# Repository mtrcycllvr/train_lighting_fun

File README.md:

## Train Car Lighting

Train Car Lighting via WS2812 based "neo pixel" like strips..
Use a couple of variable resistors to control color and brightness.
Optionally plug in LED to EOT device..

https://oshpark.com/shared_projects/cVBEIdNU 
...if you want a matching circuit board supporting Teensy 3.2 and 3.4.

Basic code is relatively simple thanks to extensive WS2812B RGB LED library support..
Read the analog values, map them to LED value ranges, push data.  Blink the
EOT device in a realistic manner..

Verision 1.3-ish..

INFO:
I purchased a USA trains "Extended Vision Caboose",
http://www.usatrains.com/r12130.html
....and decided to update and improve the lighting a little bit.  To do that, I
scavenged unsused short bits of WS2812B based RGB light strips and a "Teensy"
micro controller that you would call a super charged arduino..
https://www.pjrc.com/store/teensy40.html

I glued six each of the inegrated LED/controler (the WS2812B thing I keep referring to)
to the top of the cabboose roof separate with a small bit of wire, you only need three,
power, ground and data..

This particular model also has a built in EOT, or End Of Train device, so I am 
"poorly" using a bunch of teensy horsepower to discretely fade the EOT device on and off
so it has more of an incandescent look to it..   I rescued a vintage red glass faceted 
indicator lens to replace the stock plastic part..  Putting that together with a higher
output 5MM LED and simulated warm up and cool down really creates an AWESOME look..

The underside manufacture's three way power switch gives you the coice of just the EOT
or the EOT and interior lights.  What I WAS going to do was use SW1 to change modes, but
now I'm lazy and lucky together and I can use SW1 on half of the power switch to detect which
mode it should run in at power on..  Easy peasy, and it means I'm done  programming, which
is nice.   Wanna see more effects?  Go crazy..  I have other unfinished projects to 
attend to..  ;-)

I made a little circuit board to mount and connect the Teensy to the variable resistors,
the LED's and a power input..
https://oshpark.com/shared_projects/cVBEIdNU

Eric Timberlake - 9.10.2019

todo: Make the EOT on/off functions re-entrant so they don't interfere with reading the
variable resistors in real time..  There MUST be a nice functional event timer library 
out there someplace, right? ;-)

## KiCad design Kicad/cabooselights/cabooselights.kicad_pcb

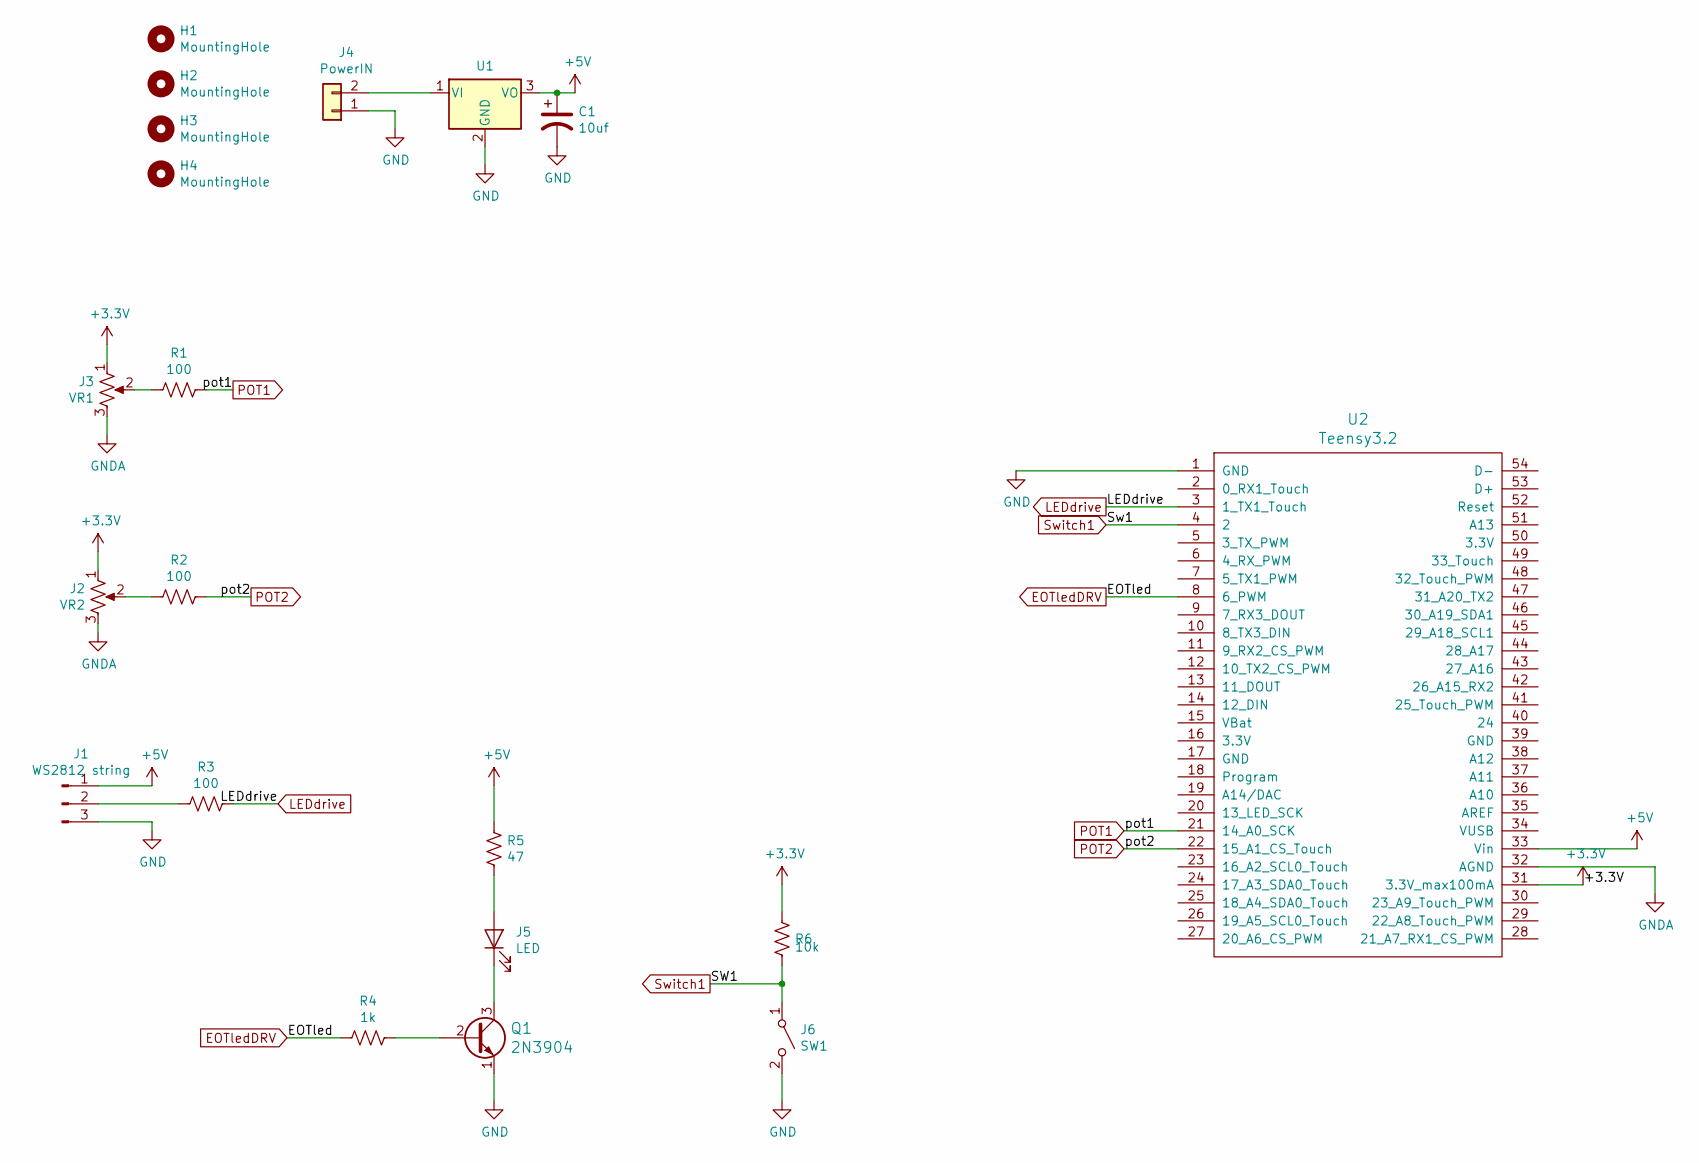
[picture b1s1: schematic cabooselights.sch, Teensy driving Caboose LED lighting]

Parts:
C1: 10uf; C_1206_3216Metric
H1, H2, H3, H4: MountingHole; MountingHole_2.7mm_M2.5
J1: WS2812 string; JST_PH_B3B-PH-K_1x03_P2.00mm_Vertical
J2: VR2; JST_PH_B3B-PH-K_1x03_P2.00mm_Vertical
J3: VR1; JST_PH_B3B-PH-K_1x03_P2.00mm_Vertical
J4: PowerIN; JST_PH_B2B-PH-K_1x02_P2.00mm_Vertical
J5: LED; JST_PH_B2B-PH-K_1x02_P2.00mm_Vertical
J6: SW1; JST_PH_B2B-PH-K_1x02_P2.00mm_Vertical
Q1: 2N3904; TO-92-3; MPN 2N3904; Digi-Key_PN 2N3904CS-ND
R1, R2, R3: 100; R_1206_3216Metric
R4: 1k; R_1206_3216Metric
R5: 47; R_Axial_DIN0204_L3.6mm_D1.6mm_P7.62mm_Horizontal
R6: 10k; R_1206_3216Metric
U1: LM7805_TO220; TO-220-3_Vertical
U2: Teensy3.2; Teensy30_31_32_LC_less_pins

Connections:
+3V3: J2.1, J3.1, R6.1, U2.31 (3.3V_max100mA)
+5V: C1.1, J1.1, R5.1, U1.3 (VO), U2.33 (Vin)
EOTledDRV: R4.2, U2.8 (6_PWM)
GND: C1.2, J1.3, J4.1, J6.2 (B), Q1.1 (E), U1.2 (GND), U2.1 (GND)
GNDA: J2.3, J3.3, U2.32 (AGND)
LEDdrive: R3.1, U2.3 (1_TX1_Touch)
unnamed: J1.2, R3.2
unnamed: J2.2, R2.2
unnamed: J3.2, R1.2
unnamed: J4.2, U1.1 (VI)
unnamed: J5.1 (K), Q1.3 (C)
unnamed: J5.2 (A), R5.2
unnamed: Q1.2 (B), R4.1
POT1: R1.1, U2.21 (14_A0_SCK)
POT2: R2.1, U2.22 (15_A1_CS_Touch)
Switch1: J6.1 (A), R6.2, U2.4 (2)

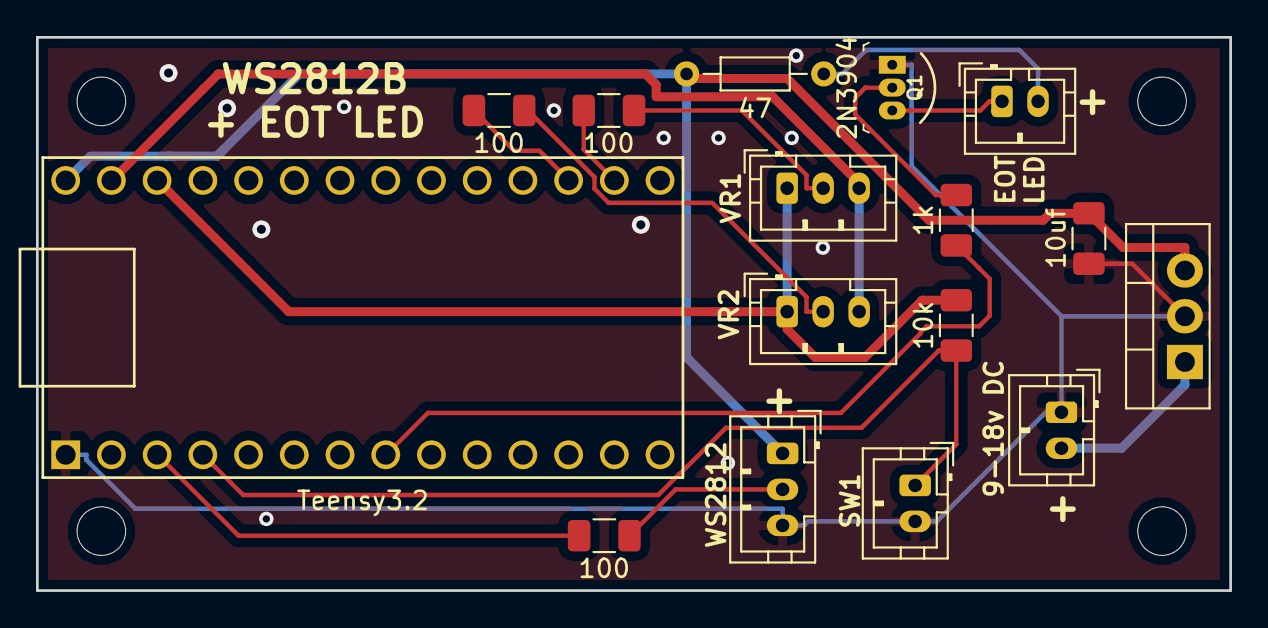
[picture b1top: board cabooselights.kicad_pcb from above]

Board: 2 copper layers, 66.3 x 30.7 mm, 20 parts (0 on the bottom side), 16 nets.

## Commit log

2019-09-12 Initial upload of simple project...
